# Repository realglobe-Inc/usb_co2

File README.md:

# usb_co2

Mac, LinuxマシンにUSBで接続できて追加ドライバ不要で値を読めるCO2センサ

## 使い方(macOS)

まず、USB機器をすべてコンピュータから取り外す。

次に、usb_co2をUSBポートに接続する。

次に、コンピュータに接続されているシリアルポートの一覧を表示する。

```
$ ls -1 /dev/cu.*
/dev/cu.Bluetooth-Incoming-Port
/dev/cu.iMiminashi5s-WirelessiAP
/dev/cu.usbmodem14101
```

上記の例の場合、`cu.usbmodem14101` というデバイスファイルがusb_co2を示す。

次に、`stty`コマンドを実行してシリアルポートの設定を行う。

```sh
stty -f /dev/cu.usbmodem14101 raw 9600
```

最後に、`cat`コマンドでデバイスファイルを読み込むとCO2の値(ppm)が表示される。

```
$ cat /dev/cu.usbmodem14101 
co2=399;status=0
co2=399;status=0
co2=399;status=0
co2=399;status=0
co2=399;status=0
co2=399;status=0
```

## 使い方(Linux)

まず、USB機器をすべてコンピュータから取り外す。

次に、usb_co2をUSBポートに接続する。

次に、コンピュータに接続されているシリアルポートの一覧を表示する。

```
$ ls -1 /dev/tty*
/dev/tty
.
. (中略)
.
/dev/ttyACM0
/dev/ttyAMA0
/dev/ttyprintk
/dev/ttyUSB0
```

上記の例の場合、`/dev/ttyACM0` というデバイスファイルがusb_co2を示す。

次に、`stty`コマンドを実行してシリアルポートの設定を行う。

```sh
stty -F /dev/ttyACM0 raw 9600
```

最後に、`cat`コマンドでデバイスファイルを読み込むとCO2の値(ppm)が表示される。

```
$ cat /dev/ttyACM0
co2=399;status=0
co2=399;status=0
co2=399;status=0
co2=399;status=0
co2=399;status=0
```

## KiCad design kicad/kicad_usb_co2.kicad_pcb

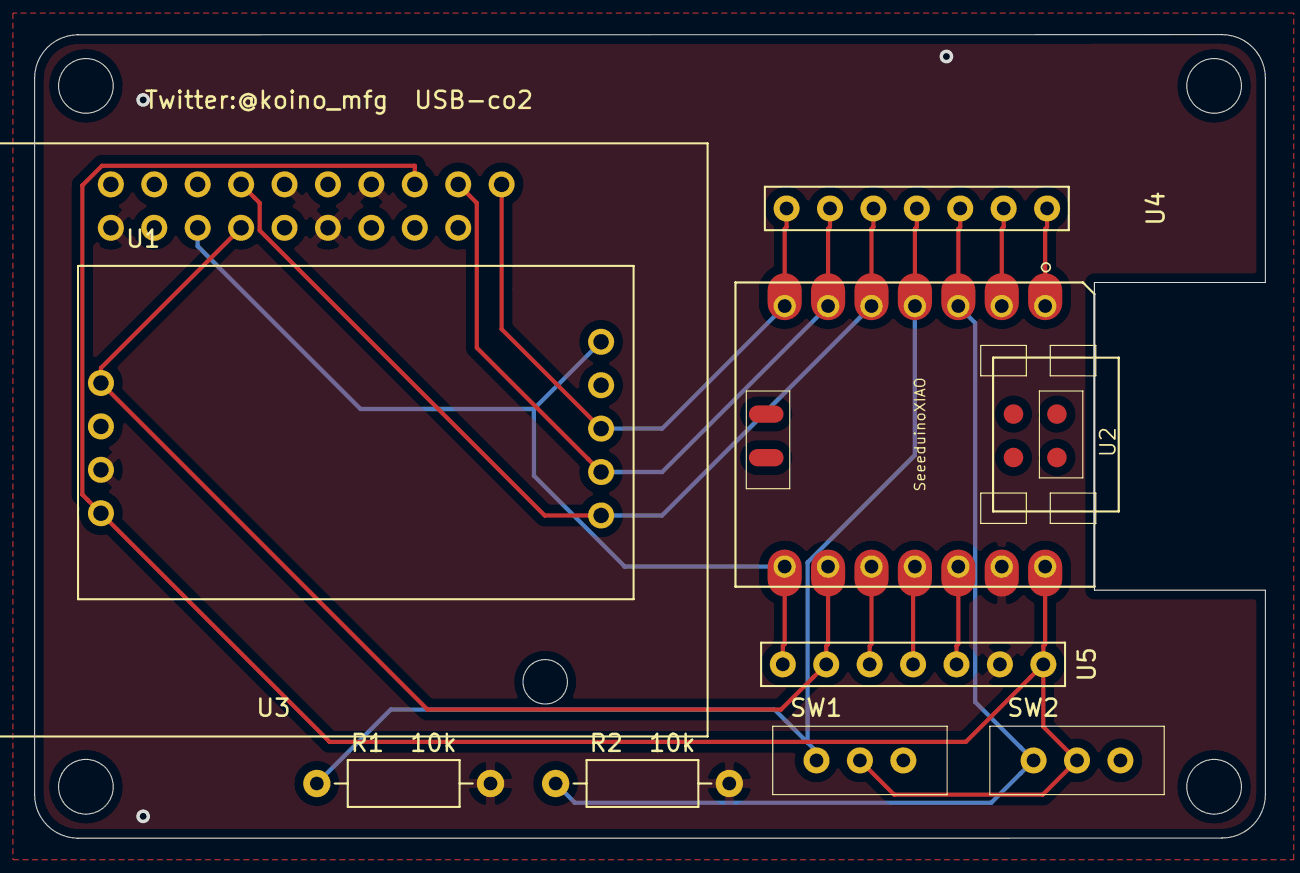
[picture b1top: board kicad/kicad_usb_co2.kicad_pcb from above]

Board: 2 copper layers, 72.0 x 47.0 mm, 9 parts (0 on the bottom side), 14 nets.

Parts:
R1  10k, R2  10k: R; R_Axial_DIN0207_L6.3mm_D2.5mm_P10.16mm_Horizontal
SW1, SW2: SW_SPDT; SW_SLIDE_sengoku
U1: MH-Z19B
U2: SeeeduinoXIAO; SeeedXIAO
U3: MH-Z14A
U4, U5: PinHeader_XIAO

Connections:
+5V: SW1.2, SW2.2, U1.9, U2.14, U3.17, U5.7
GND: R1 10k.2, R2 10k.2, U1.8, U2.13, U3.2, U3.3, U3.12, U3.16, U5.6
unnamed: R1 10k.1, SW1.1, U2.4, U4.4
unnamed: R2 10k.1, SW2.1, U2.3, U4.3
unnamed: U1.1, U2.8, U3.8, U5.1
unnamed: U1.3, U2.7, U3.19, U4.7
unnamed: U1.4, U2.6, U3.18, U4.6
unnamed: U1.5, U2.5, U3.5, U4.5
unnamed: U1.6, U2.9, U3.6, U5.2
unnamed: U2.1, U4.1
unnamed: U2.2, U4.2
unnamed: U2.10, U5.3
unnamed: U2.11, U5.4
unnamed: U2.12, U5.5

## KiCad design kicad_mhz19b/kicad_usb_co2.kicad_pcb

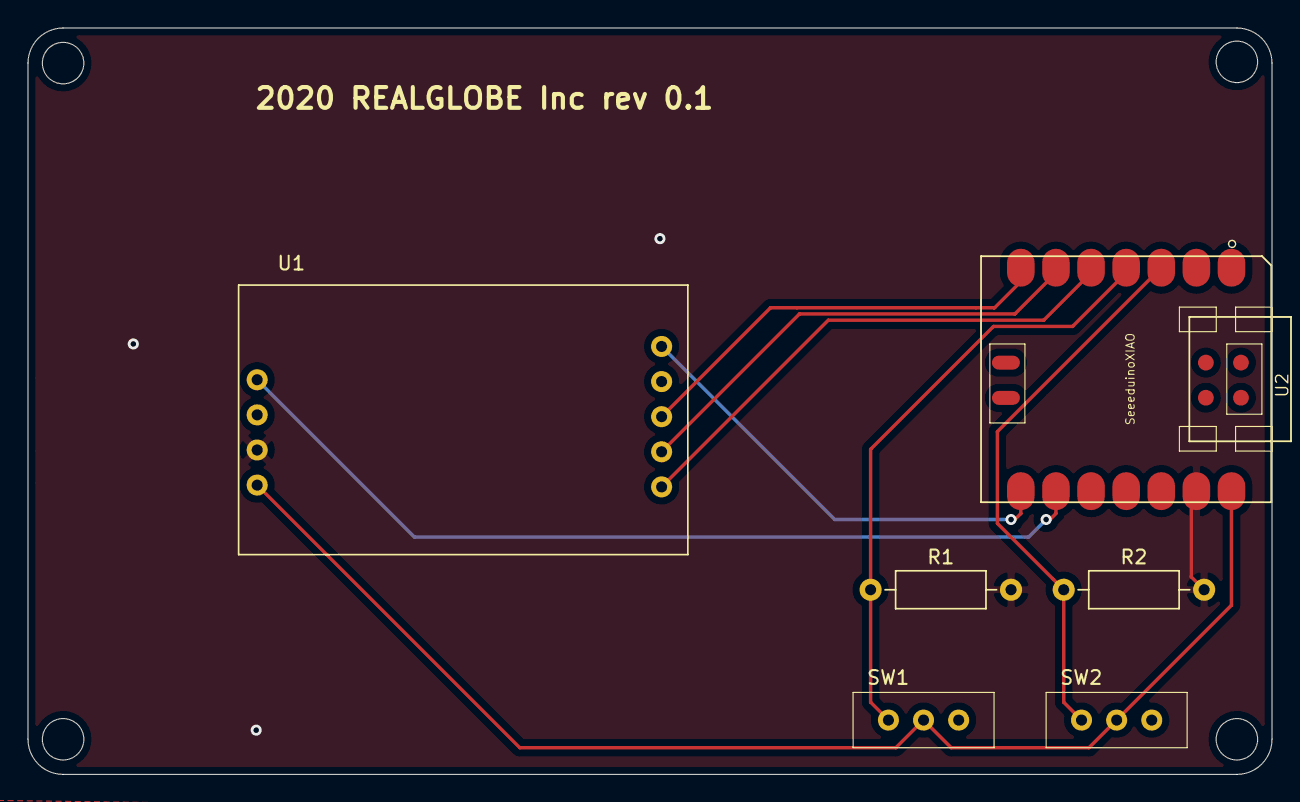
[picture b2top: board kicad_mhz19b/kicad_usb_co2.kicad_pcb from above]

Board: 2 copper layers, 90.0 x 54.0 mm, 6 parts (0 on the bottom side), 9 nets.

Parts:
R1, R2: R; R_Axial_DIN0207_L6.3mm_D2.5mm_P10.16mm_Horizontal
SW1, SW2: SW_SPDT; SW_SLIDE_sengoku
U1: MH-Z19B
U2: SeeeduinoXIAO; Seeeduino XIAO-MOUDLE14P-2.54-21X17.8MM

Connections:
+5V: SW1.2, SW2.2, U1.9, U2.14
GND: R1.2, R2.2, U1.8, U2.13
unnamed: R1.1, SW1.1, U2.4
unnamed: R2.1, SW2.1, U2.3
unnamed: U1.1, U2.8
unnamed: U1.3, U2.7
unnamed: U1.4, U2.6
unnamed: U1.5, U2.5
unnamed: U1.6, U2.9

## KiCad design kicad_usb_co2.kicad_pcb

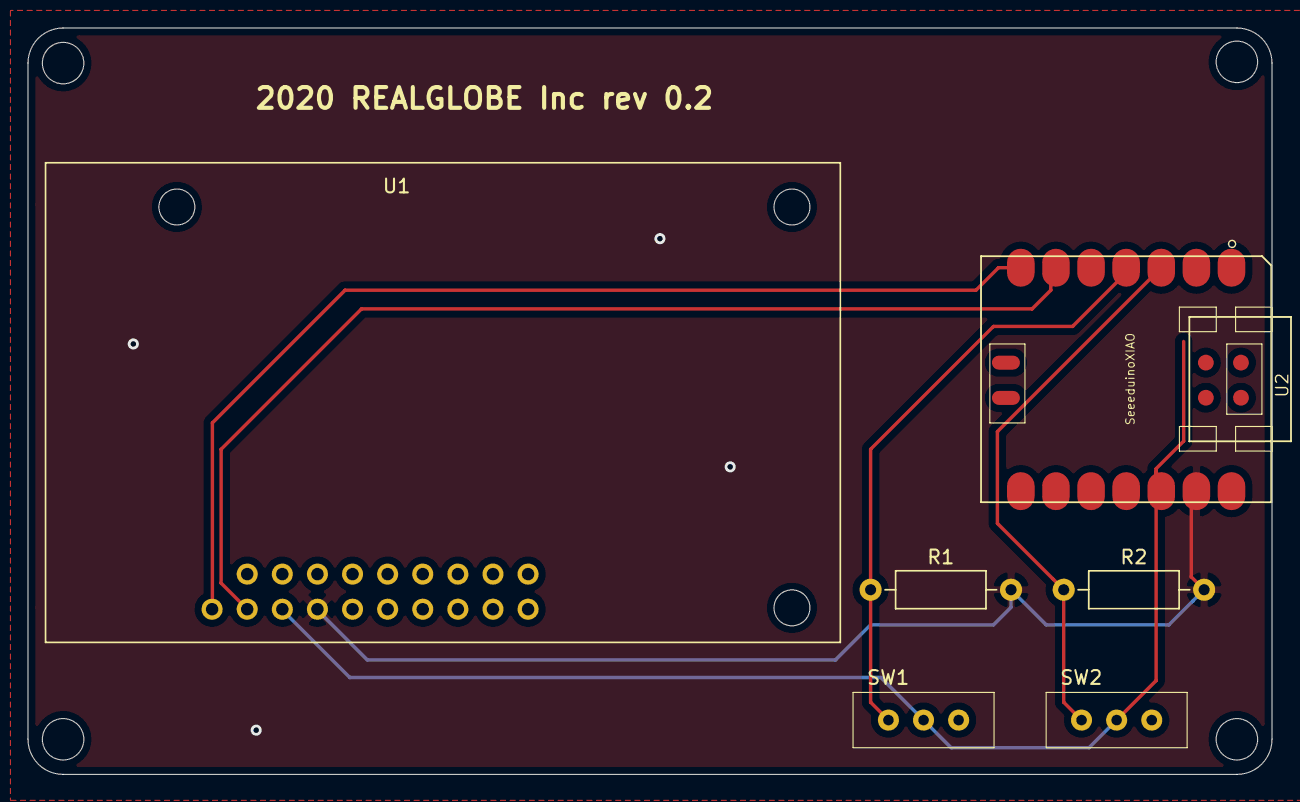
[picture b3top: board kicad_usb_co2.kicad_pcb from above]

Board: 2 copper layers, 90.0 x 54.0 mm, 6 parts (0 on the bottom side), 6 nets.

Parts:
R1, R2: R; R_Axial_DIN0207_L6.3mm_D2.5mm_P10.16mm_Horizontal
SW1, SW2: SW_SPDT; SW_SLIDE_sengoku
U1: MH-Z14A
U2: SeeeduinoXIAO; Seeeduino XIAO-MOUDLE14P-2.54-21X17.8MM

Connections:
+3V3: SW1.2, SW2.2, U1.17, U2.12
GND: R1.2, R2.2, U1.16, U2.13
unnamed: R1.1, SW1.1, U2.4
unnamed: R2.1, SW2.1, U2.3
unnamed: U1.18, U2.6
unnamed: U1.19, U2.7

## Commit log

2020-03-28 ProMicroに対応した
2020-03-30 出力フォーマットを変更した
2020-05-25 Seeduino XIAOに対応した
2020-06-22 kicadのデータ作った
2020-07-08 不要なファイルを削除
2020-07-08 update update
2020-07-08 不要なので削除
2020-07-28 add vscode
2020-07-28 MH-Z14Aの制御を別ファイルに移動
2020-07-28 MH-Z14Aのinit するの忘れてた
2020-07-28 MH-Z14Aの送信-受信待ちは実測3msなので100→10msへ変更
2020-07-28 送信コマンドをファイルスコープにした
2020-07-28 起動時にMH-Z14Aの自動校正機能(ABC)をOFFにするコードを追加
2020-07-28 ゼロ校正関数を追加
2020-07-31 ゼロ校正関数内で１秒毎にCO2値を空読みして30分経過後ゼロ校正をするよう変更
2020-07-31 LEDとスイッチの定義と初期化を追加
2020-07-31 SW1押下しながらの起動でゼロ校正をする
2020-08-03 基板四隅の面取りとネジ穴をM3にした
2020-08-04 MH-Z14Aのフットプリントを更新
2020-08-16 画像を追加した
2020-08-16 markdownの誤記をなおした
2020-08-16 画像の大きさを変更した
2020-08-19 LEDを削除、タクトスイッチからトグルスイッチに変更
2020-08-20 ガーバー出力オプション変更
2020-09-17 自動校正をONにする関数の追加
2020-09-17 起動時に自動校正をOFFにするのをやめた
2020-09-17 手動校正モードに入らないようにした
2020-09-17 外付けLEDを無くしてボード上のLEDを使用するようにした
2020-09-17 シリアル接続を確立してからセンサの初期化をするようにした
2020-09-17 シリアル出力にステータスをつけた
2020-09-21 READMEに使い方を記載した
2020-09-21 Linux版の使い方を記載した
2020-09-25 シリアル出力の改行コードを変更した
2020-10-02 kicadのファイルをMH-Z14AとMH-Z19Bで分けた
2020-10-02 MH-Z14Aのファイルをコピーした
2020-10-05 MH-Z14A→MH-Z19Bへ置き換え、ERC OK、フットプリント関連付けはまだ
2020-10-15 スキーマ引き直した
2020-10-15 センサの電源を3.3Vから5Vに変えた
2020-10-15 配置配線ok DRCok
2020-10-15 ちょっといじっちゃったので戻した
2020-10-15 バージョンがrev 0.2 のままだったので、0.1に治した
2020-10-23 ABCをonにするつもりでoffにしている箇所を修正した
2020-10-23 なんもなおせてなかった
2020-10-28 kicadのフォルダをMH-Z14Aと19Bと共通にした
2020-10-28 スキーマにMH-Z14AとMH-Z19Bを共存させた
2020-10-28 XIAOのピンをすべてピンヘッダに出した
2020-10-28 ピンヘッダのフットプリントが関連付いてなかった
2020-10-28 色々フットプリントが関連付いてなかった
2020-10-28 基板外形の修正と仮配置
2020-10-28 たぶん動く
2020-10-30 シルクのリビジョンをインクリした
2020-11-09 配列の初期化忘れ
2020-11-09 CO2値を戻り値でなく参照渡しにした
2020-11-11 ドライバ側で時間を持たないようにした(ノンブロッキングにした9
2020-11-11 ドライバの修正に合わせた
2021-01-27 MH-Z19のスルーホールを大きくした
2021-01-27 抵抗の容量をシルクで書いた
2021-01-27 基板リビジョンシルクをインクリメントした
2021-02-22 センサリセット時に1回目のデータを捨てるようにした
2021-02-22 現行基板の写真に差し替え
2021-05-04 署名を変更
2021-06-06 フォーマッタかけた
2021-06-06 シリアル出力にバージョンを追加した(1.00)
